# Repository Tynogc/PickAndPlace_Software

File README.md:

# PickAndPlace_Software
A Java Program to Control the Pick&amp;Place-Machine

This Program uses OpenCV and has some Open-Fonts in it.

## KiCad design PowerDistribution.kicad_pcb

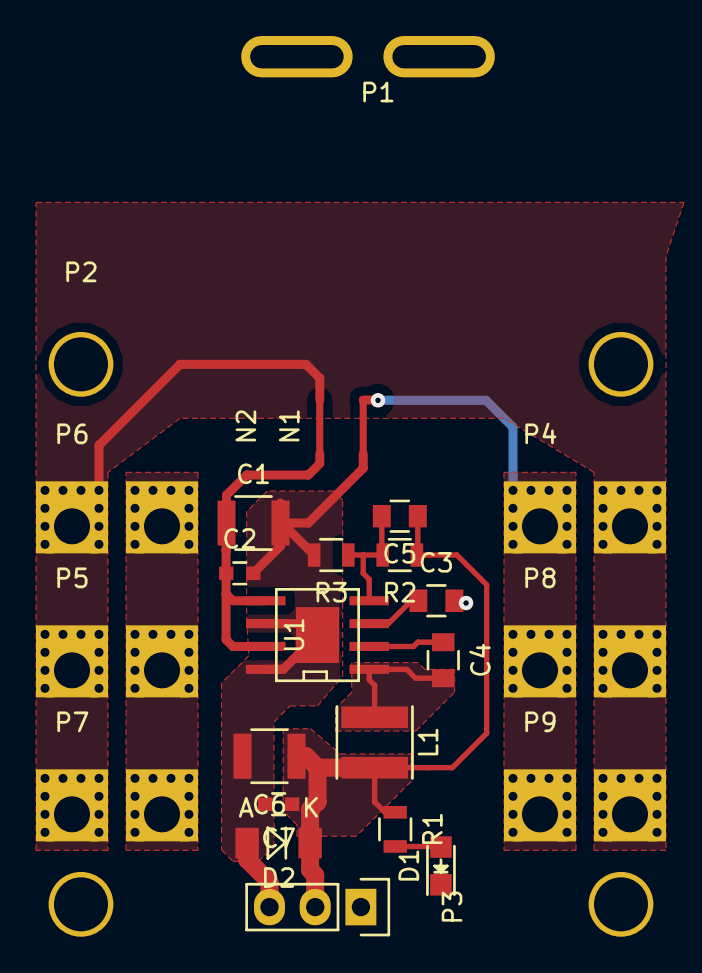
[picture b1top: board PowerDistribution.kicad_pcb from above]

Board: 2 copper layers, 25 parts (0 on the bottom side), 10 nets.

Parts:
C1: Cin; C_1210
C2: Cin100nf; C_0603
C3: Cvcc; C_0805
C4: Cboot; C_0805
C5: Cff; C_0805
C6: Cout; C_1210
C7: Cout100nf; C_0603
D1: LED; LED_0805
D2: TVS; MiniMELF_Standard
L1: L; Inductor_Taiyo-Yuden_MD-4040
N1, N2: NetTie; NetTie-04
P1: CONN_01X02; PowerPole_1x2
P2: CONN_01X01; Mounting_30x30
P3: CONN_01X03; Pin_Header_Straight_1x03
P4, P5, P6, P7, P8, P9: CONN_01X02; Conn_HC_2
R1: R; R_0805
R2: Rfbt; R_0805
R3: Rrfbb; R_0805
U1: LMR23625CDDA; HSOIC-8-Pad

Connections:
+5V: C5.1, C6.1, C7.1, D2.1, L1.2, P3.2, R1.1, R2.1
+12V: N2.1, P1.2, P4.2, P5.1, P6.1, P7.1, P8.2, P9.2
/FB: C5.2, R2.2, R3.1, U1.4
/Power_In: C1.1, C2.1, N2.2, U1.5, U1.7
/SW: C4.2, L1.1, U1.1
GND: C1.2, C2.2, C3.2, C6.2, C7.2, D1.1, D2.2, N1.2, P3.3, R3.2, U1.6, U1.8, U1.9
GNDPWR: N1.1, P1.1, P4.1, P5.2, P6.2, P7.2, P8.1, P9.1
unnamed: C3.1, U1.3
unnamed: C4.1, U1.2
unnamed: D1.2, R1.2

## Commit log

2016-12-06 Update LICENSE
2016-12-06 Added Comunication besics
2016-12-07 Fixed Connection Problems
2016-12-08 1st sucessfull Edge-Detector test
2016-12-08 minor adj. to the Algorithm
2016-12-08 Changed Java-Version to 1.6 and other minor adjustments
2016-12-08 Splitet FootprintPainter in FootprintSize/Painter
2016-12-08 Added Spindel and Spindel settup
2016-12-08 Minor Adjustments
2016-12-09 minor things...
2016-12-10 Beter Rotation-Detection-Algorithm
2016-12-11 First Succesfull test of Part-Placement!
2016-12-11 Added Reels and Footprint selection
2016-12-12 Advanced the Part-Detection
2016-12-12 minor stuff
2016-12-12 Major Change to Part-Detection 100% working now!
2016-12-13 Gui and stuff
2016-12-13 Advanced part-Detection: PUE
2016-12-13 Added DropDownMenu
2016-12-13 added isVisible Check
2016-12-13 Gui ect.
2016-12-13 little fix
2016-12-14 minor things
2016-12-14 advanced gui
2016-12-15 Changed Button methods and added Container
    Fix Programming for add() and remove() ect.
2016-12-19 ReelSetup Changed
2016-12-20 Added PCB import
2016-12-20 Minor Coding
2016-12-20 Added Modular Project Viewer
2016-12-20 Generated Project Classes
2016-12-21 Project and Components advanced
2016-12-21 Added File System for Components and minor stuff
2016-12-22 Prepared .dsn-Support and advanced GUI
2016-12-22 Fixed Null Pointer Exeption
2016-12-22 Fixed Menu priority bugs
2016-12-24 Added Quick-Barcode accsess
2016-12-24 Added Machine Process Structure
2016-12-26 Added CSV-import and prepared Post-Processor
2016-12-26 Added Text-Box
2016-12-28 Advanced Setup, added Reel/Tube/Tray-Menu
2016-12-28 added name tag
2016-12-29 Vreated VERSION-String
2016-12-30 added PostProcessor
2017-01-11 Added License Notification and advanced Debug
2017-02-01 Started Communication and minor stuff
2017-02-02 Started Processing
2017-02-25 Added No-Log Debug Informations; Changed Layout of IPCtoCNC
2019-11-30 This is only a Test
